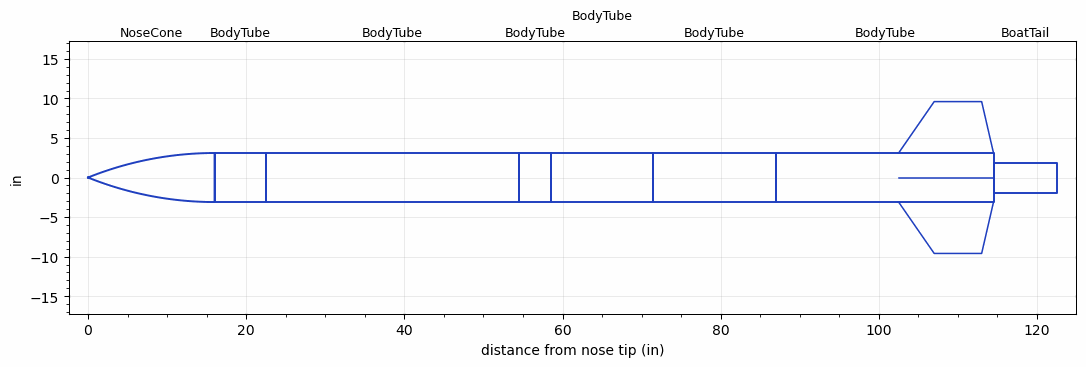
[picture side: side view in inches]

<RASAeroDocument>
 <FileVersion>2</FileVersion>
 <RocketDesign>
  <NoseCone>
   <Length>16</Length>
   <Diameter>6.2</Diameter>
   <Shape>Tangent Ogive</Shape>
   <Location>0</Location>
  </NoseCone>
  <BodyTube>
   <Length>6.5</Length>
   <Diameter>6.2</Diameter>
   <Location>16</Location>
  </BodyTube>
  <BodyTube>
   <Length>31.9999</Length>
   <Diameter>6.2</Diameter>
   <Location>22.5</Location>
  </BodyTube>
  <BodyTube>
   <Length>4</Length>
   <Diameter>6.2</Diameter>
   <Location>54.4999</Location>
  </BodyTube>
  <BodyTube>
   <Length>13</Length>
   <Diameter>6.2</Diameter>
   <Location>58.4999</Location>
  </BodyTube>
  <BodyTube>
   <Length>15.5</Length>
   <Diameter>6.2</Diameter>
   <Location>71.4999</Location>
  </BodyTube>
  <BodyTube>
   <Length>27.4999</Length>
   <Diameter>6.2</Diameter>
   <RailGuideDiameter>0.621</RailGuideDiameter>
   <RailGuideHeight>0.6845</RailGuideHeight>
   <Location>86.9998</Location>
   <Fin>
    <Count>4</Count>
    <Chord>12</Chord>
    <Span>6.5</Span>
    <SweepDistance>4.5</SweepDistance>
    <TipChord>6</TipChord>
    <Thickness>0.25</Thickness>
    <Location>12</Location>
    <AirfoilSection>Rounded</AirfoilSection>
   </Fin>
  </BodyTube>
  <BoatTail>
   <Length>8</Length>
   <Diameter>3.8</Diameter>
   <RearDiameter>3.8</RearDiameter>
   <Location>114.4998</Location>
  </BoatTail>
  <Surface>Sheet Metal</Surface>
  <CD>0</CD>
  <ModifiedBarrowman>False</ModifiedBarrowman>
  <Turbulence>False</Turbulence>
  <UseBooster1>False</UseBooster1>
  <UseBooster2>False</UseBooster2>
 </RocketDesign>
 <LaunchSite>
  <Altitude>2870.735</Altitude>
  <Pressure>28.9828</Pressure>
  <RodAngle>5</RodAngle>
  <RodLength>163.9997</RodLength>
  <Temperature>77</Temperature>
  <WindSpeed>15</WindSpeed>
 </LaunchSite>
 <Recovery>
  <Altitude1>1476.378</Altitude1>
  <Altitude2>656.168</Altitude2>
  <DeviceType1>Parachute</DeviceType1>
  <DeviceType2>Parachute</DeviceType2>
  <Event1>True</Event1>
  <Event2>True</Event2>
  <Size1>95.9998</Size1>
  <Size2>22.9</Size2>
  <EventType1>Altitude</EventType1>
  <EventType2>Apogee</EventType2>
  <CD1>2.19</CD1>
  <CD2>0</CD2>
 </Recovery>
 <SimulationList>
  <Simulation>
   <SustainerLaunchWt>61.4199</SustainerLaunchWt>
   <SustainerCG>74.1841</SustainerCG>
   <SustainerIgnitionDelay>0</SustainerIgnitionDelay>
   <Booster1SeparationDelay>0</Booster1SeparationDelay>
   <Booster1IgnitionDelay>0</Booster1IgnitionDelay>
   <IncludeBooster1>False</IncludeBooster1>
   <Booster2Delay>0</Booster2Delay>
   <IncludeBooster2>False</IncludeBooster2>
  </Simulation>
 </SimulationList>
</RASAeroDocument>
